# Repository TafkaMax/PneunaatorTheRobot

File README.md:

# PneunaatorTheRobot
Say hello to my little pneunaator.

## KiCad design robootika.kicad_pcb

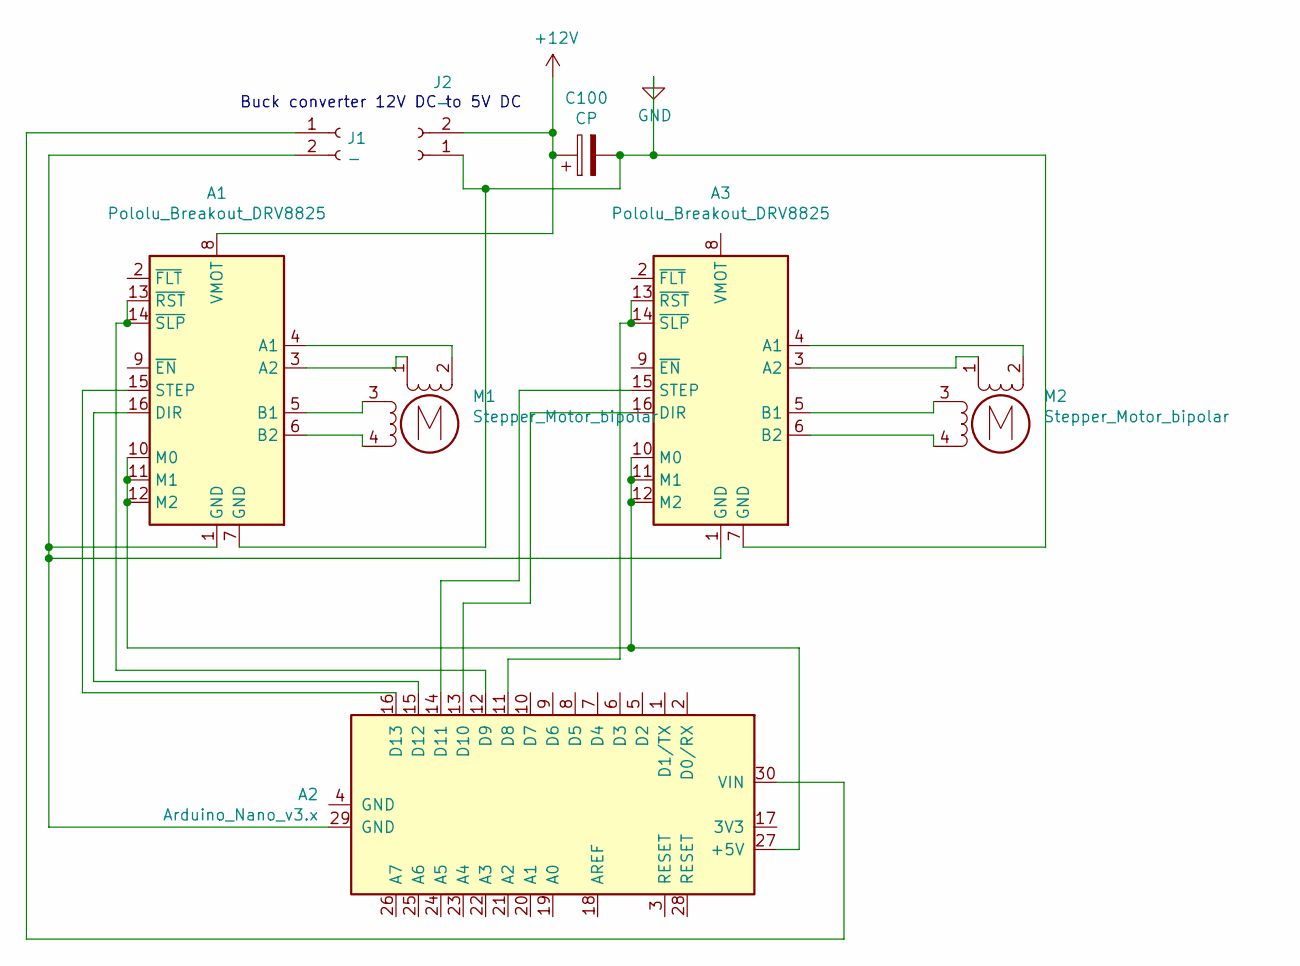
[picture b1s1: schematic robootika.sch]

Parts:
A1, A3: Pololu_Breakout_DRV8825; Pololu_Breakout-16_15.2x20.3mm
A2: Arduino_Nano_v3.x; Arduino_Nano
C100: CP; CP_Radial_D8.0mm_P3.50mm
J1, J2: -; PinSocket_1x02_P2.54mm_Vertical
M1, M2: Stepper_Motor_bipolar; TerminalBlock_RND_205-00003_1x04_P5.00mm_Horizontal

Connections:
+12V: A1.8 (VMOT), C100.1, J2.2
GND: A1.7 (GND), A3.7 (GND), C100.2, J2.1
unnamed: A1.1 (GND), A2.29 (GND), A3.1 (GND), J1.2
unnamed: A1.3 (A2), M1.1
unnamed: A1.4 (A1), M1.2 (-)
unnamed: A1.5 (B1), M1.3
unnamed: A1.6 (B2), M1.4
unnamed: A1.10 (M0), A1.11 (M1), A1.12 (M2), A2.27 (+5V), A3.10 (M0), A3.11 (M1), A3.12 (M2)
unnamed: A1.13 (~RST), A1.14 (~SLP), A2.12 (D9)
unnamed: A1.15 (STEP), A2.16 (D13)
unnamed: A1.16 (DIR), A2.15 (D12)
unnamed: A2.11 (D8), A3.13 (~RST), A3.14 (~SLP)
unnamed: A2.13 (D10), A3.16 (DIR)
unnamed: A2.14 (D11), A3.15 (STEP)
unnamed: A2.30 (VIN), J1.1
unnamed: A3.3 (A2), M2.1
unnamed: A3.4 (A1), M2.2 (-)
unnamed: A3.5 (B1), M2.3
unnamed: A3.6 (B2), M2.4

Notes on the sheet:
Buck converter 12V DC to 5V DC

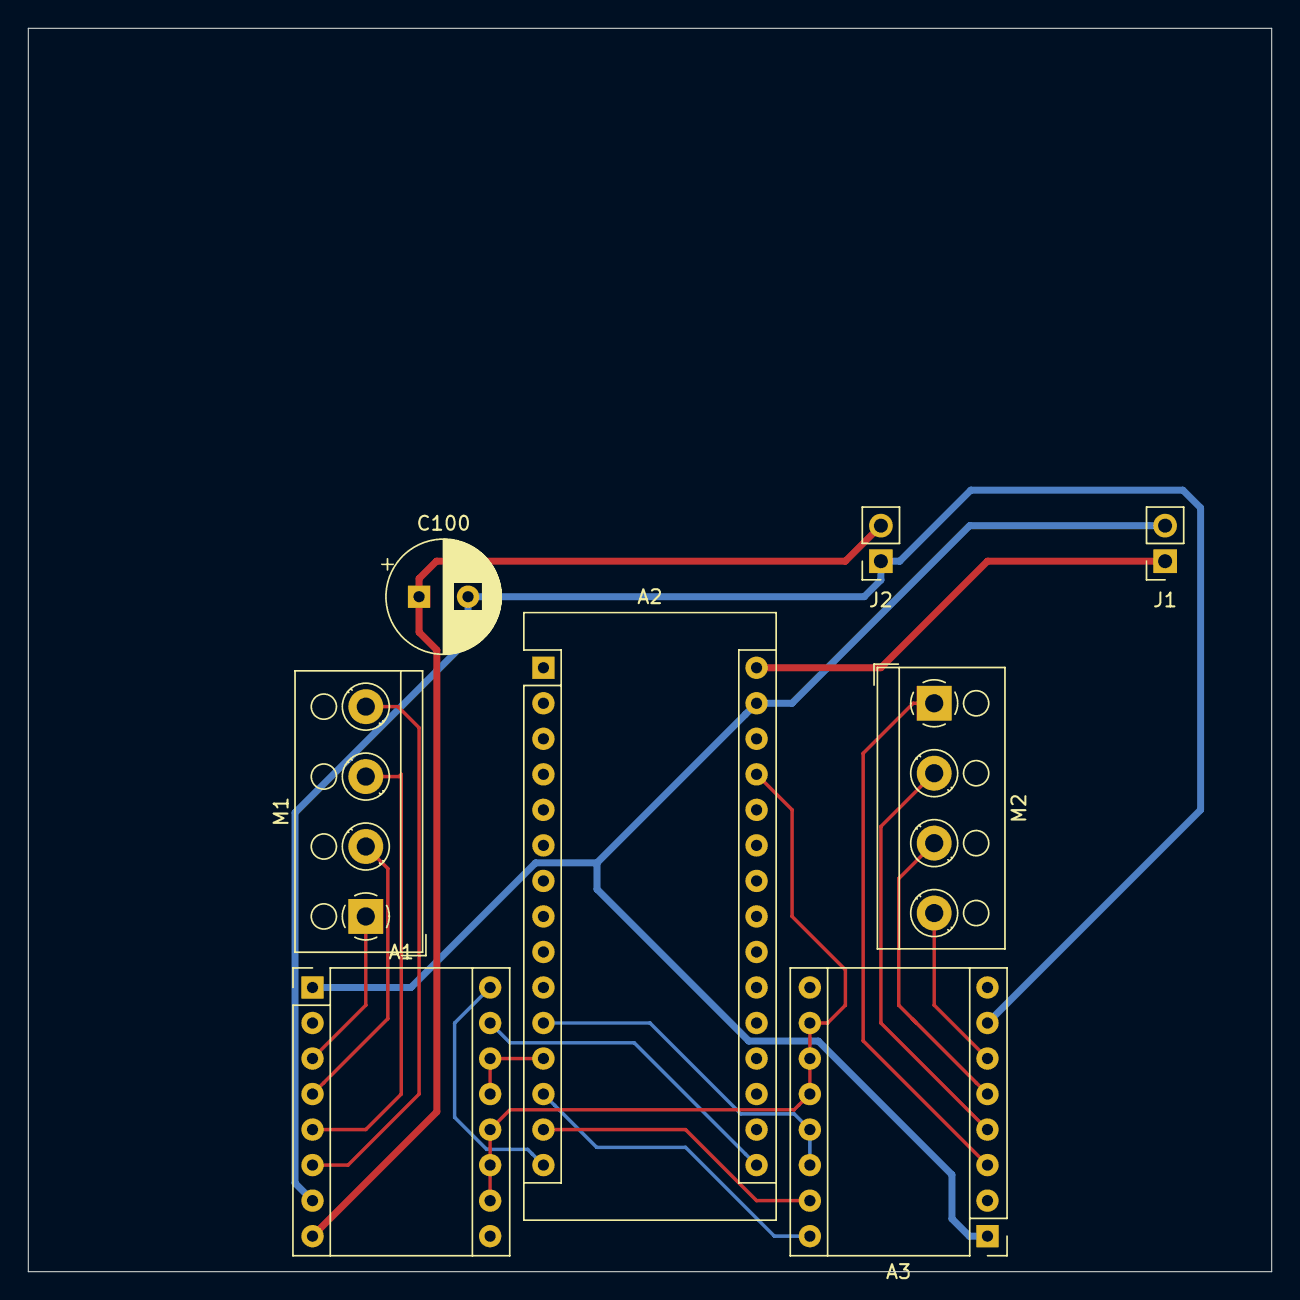
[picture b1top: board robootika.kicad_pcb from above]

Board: 2 copper layers, 88.9 x 88.9 mm, 8 parts (0 on the bottom side), 19 nets.

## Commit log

2020-03-02 Added KiCad PCB files
